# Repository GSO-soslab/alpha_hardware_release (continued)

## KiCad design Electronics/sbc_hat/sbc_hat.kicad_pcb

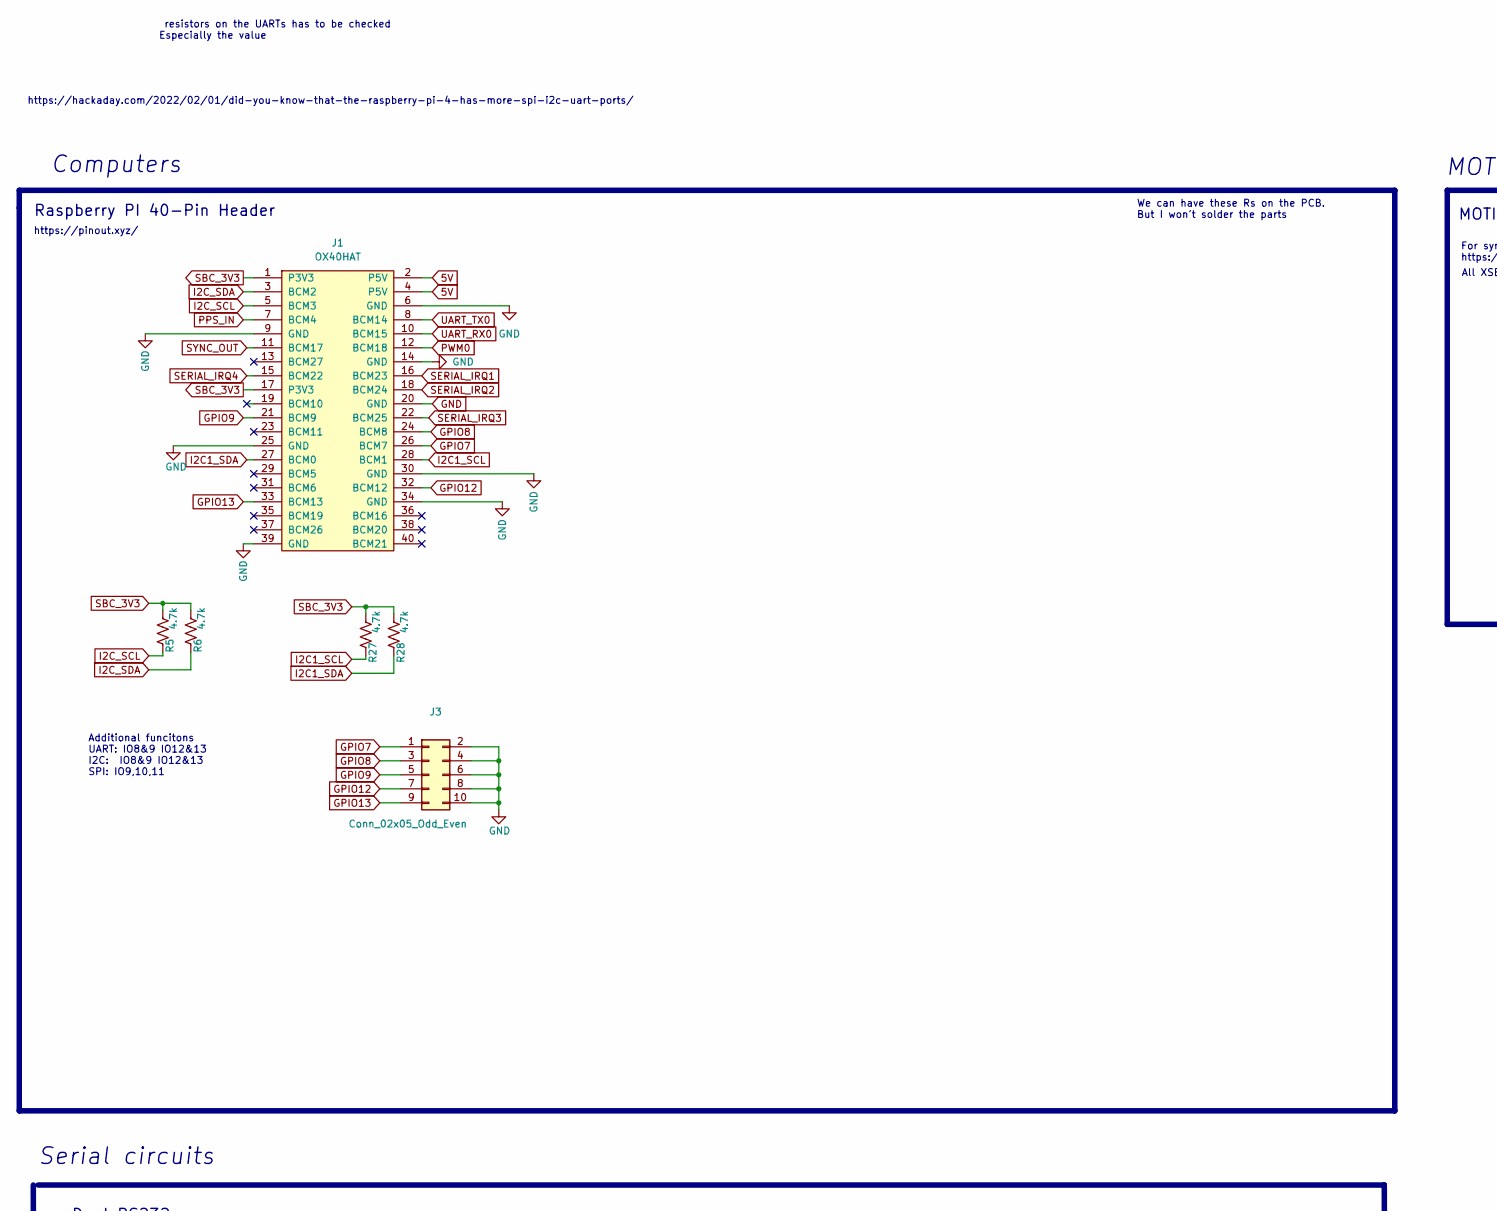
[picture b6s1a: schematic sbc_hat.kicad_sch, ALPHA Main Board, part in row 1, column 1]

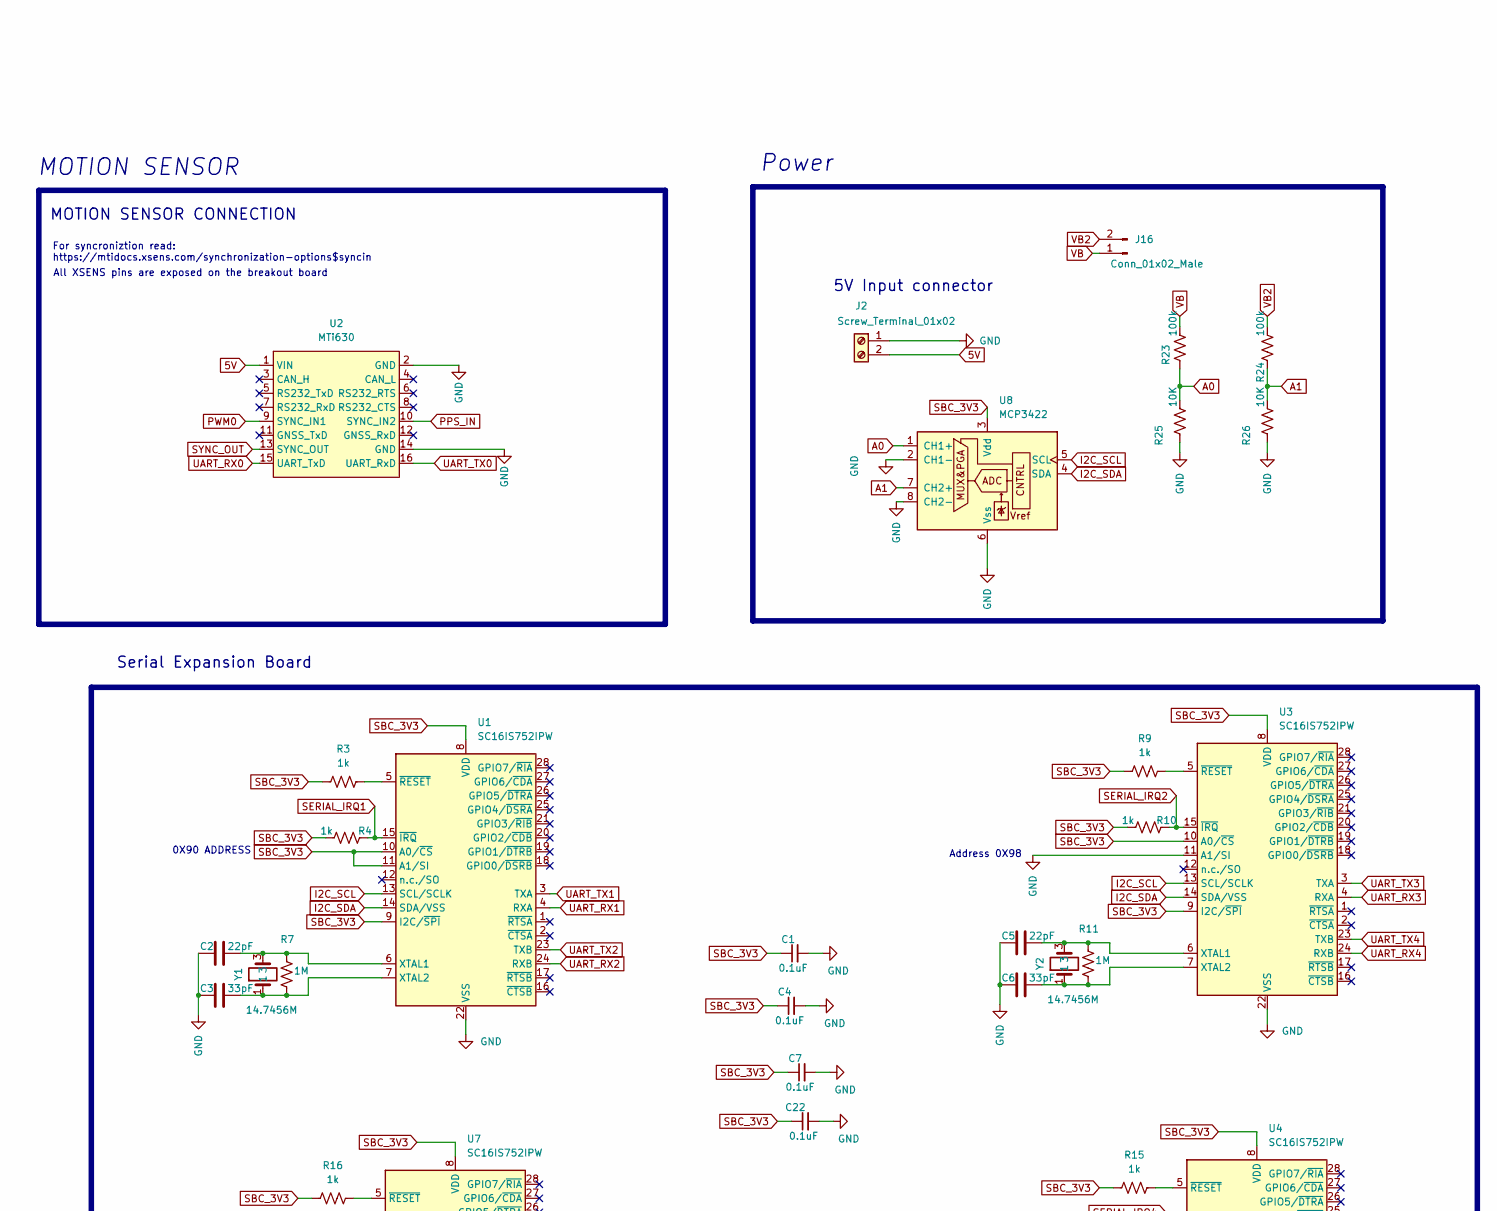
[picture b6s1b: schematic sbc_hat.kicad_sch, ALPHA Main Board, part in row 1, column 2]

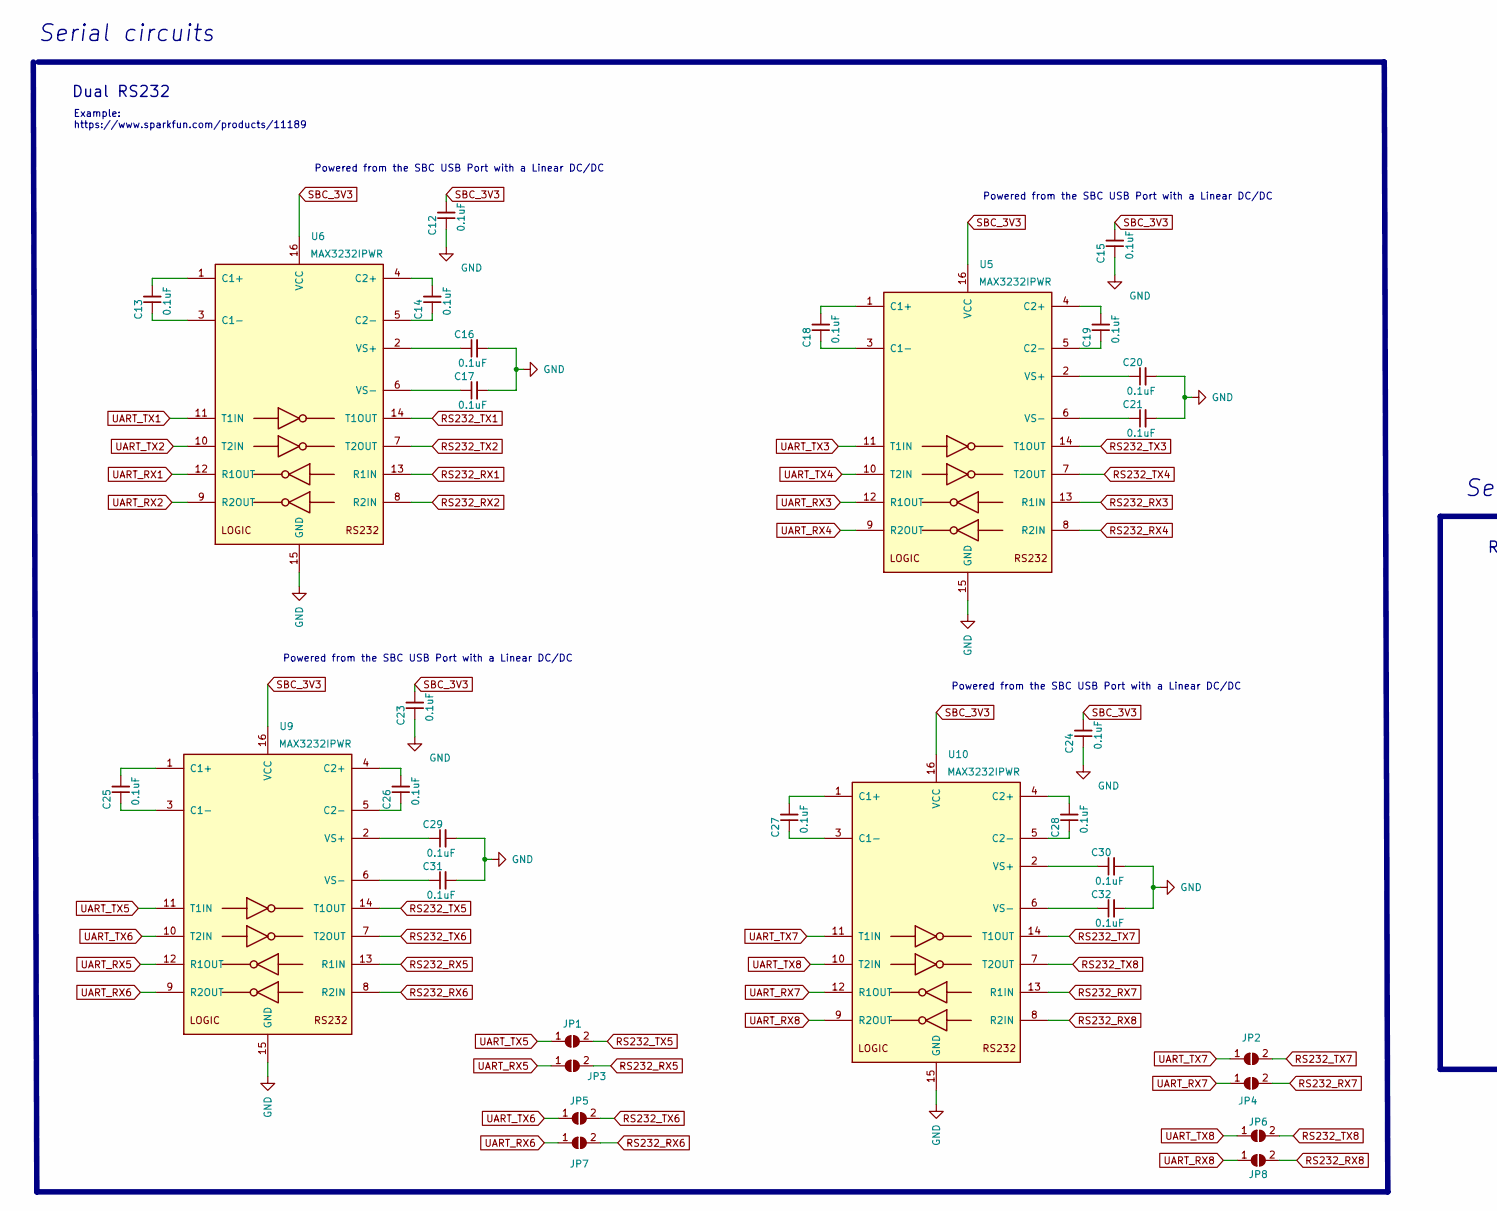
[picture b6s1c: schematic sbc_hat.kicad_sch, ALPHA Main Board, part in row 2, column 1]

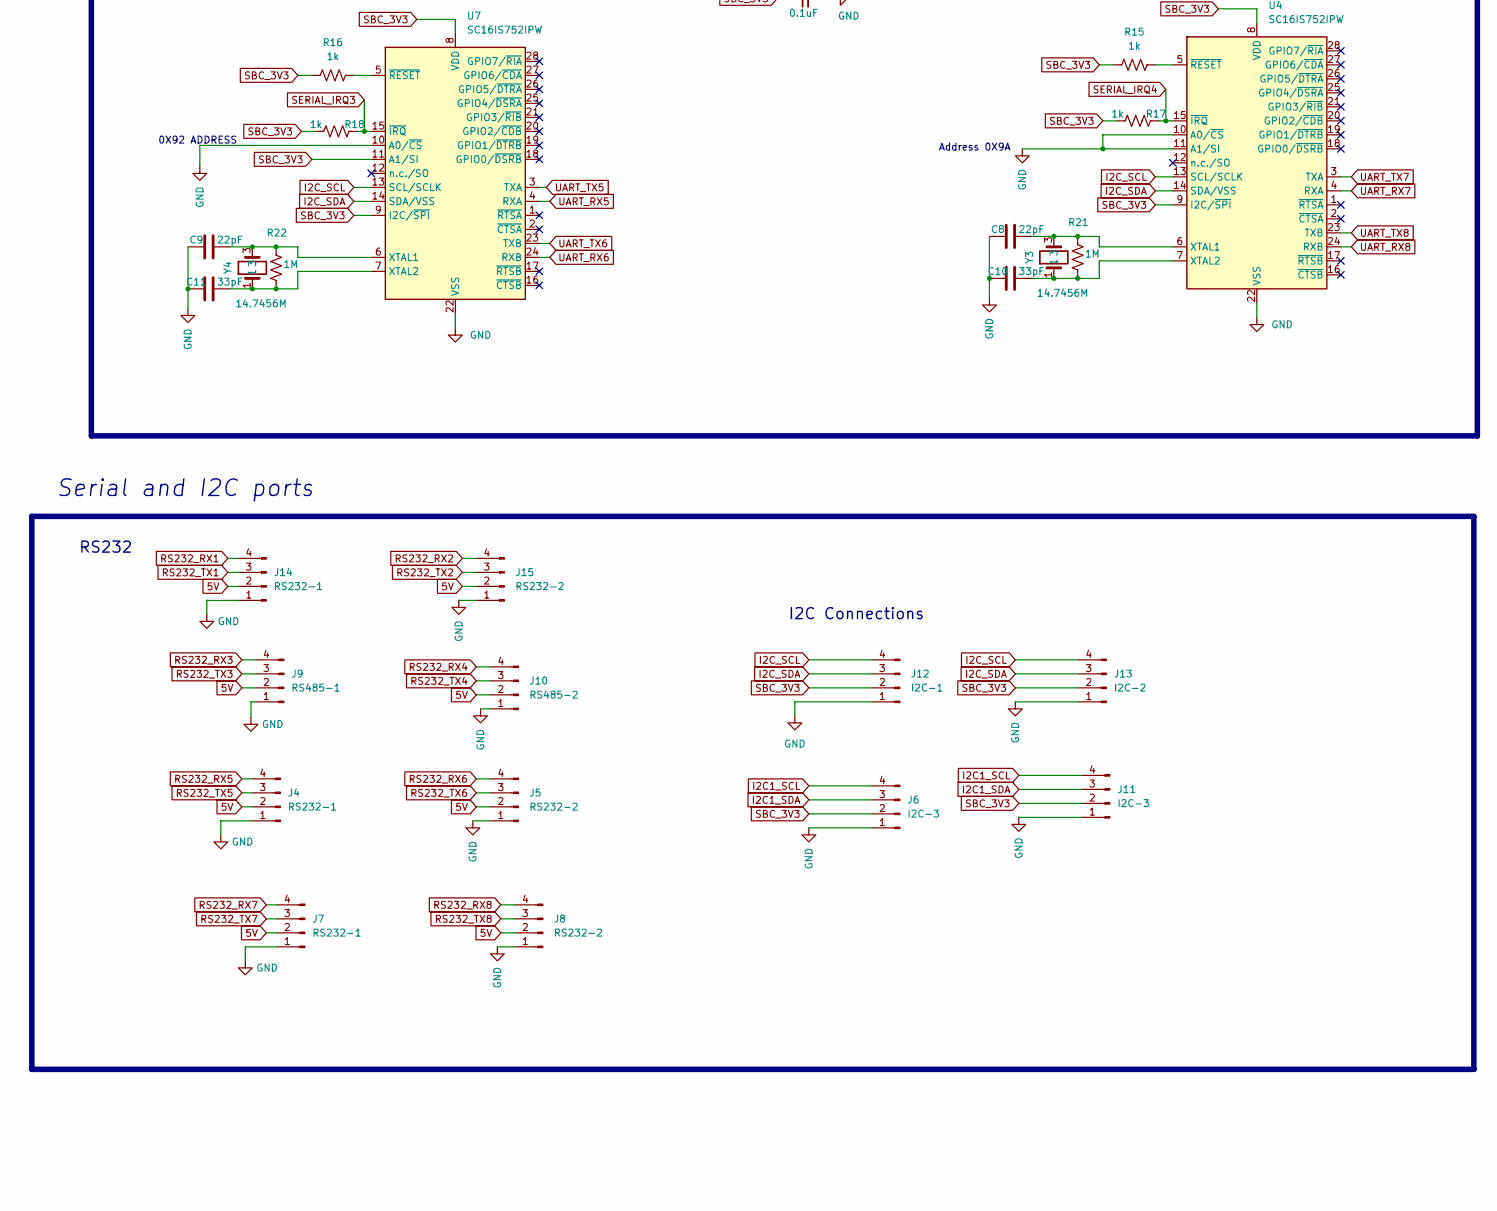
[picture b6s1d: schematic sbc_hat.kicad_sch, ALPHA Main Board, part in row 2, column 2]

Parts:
C1, C4, C7, C12, C13, C14, C15, C16, C17, C18, C19, C20, C21, C22, C23, C24, C25, C26, C27, C28, C29, C30, C31, C32: 0.1uF; C_0805_2012Metric; Manufacturer_Part_Number 0805ZC104JAT2A; Digikey Part Number 478-11627-1-ND
C2, C5, C8, C9: 22pF; C_0805_2012Metric; Manufacturer_Part_Number 08055J220FBTTR; Digikey Part Number 478-11911-1-ND
C3, C6, C10, C11: 33pF; C_0805_2012Metric; Manufacturer_Part_Number 600F330FT250XT; Digikey Part Number 1284-1049-1-ND
J1: OX40HAT; PinSocket_2x20_P2.54mm_Vertical; Mouser Part Number 474-PRT-14017
J2: Screw_Terminal_01x02; TerminalBlock_Phoenix_MPT-0,5-2-2.54_1x02_P2.54mm_Horizontal; Manufacturer_Part_Number 1725656; Mouser Part Number 651-1725656
J3: Conn_02x05_Odd_Even; PinHeader_2x05_P2.54mm_Vertical
J4, J7, J14: RS232-1; JST_SH_BM04B-SRSS-TB_1x04-1MP_P1.00mm_Vertical; Manufacturer_Part_Number 4328; Digikey Part Number 1528-4328-ND
J5, J8, J15: RS232-2; JST_SH_BM04B-SRSS-TB_1x04-1MP_P1.00mm_Vertical; Manufacturer_Part_Number 4328; Digikey Part Number 1528-4328-ND
J6, J11: I2C-3; JST_SH_BM04B-SRSS-TB_1x04-1MP_P1.00mm_Vertical; Manufacturer_Part_Number 4328; Digikey Part Number 1528-4328-ND
J9: RS485-1; JST_SH_BM04B-SRSS-TB_1x04-1MP_P1.00mm_Vertical; Manufacturer_Part_Number 4328; Digikey Part Number 1528-4328-ND
J10: RS485-2; JST_SH_BM04B-SRSS-TB_1x04-1MP_P1.00mm_Vertical; Manufacturer_Part_Number 4328; Digikey Part Number 1528-4328-ND
J12: I2C-1; JST_SH_BM04B-SRSS-TB_1x04-1MP_P1.00mm_Vertical; Manufacturer_Part_Number 4328; Digikey Part Number 1528-4328-ND
J13: I2C-2; JST_SH_BM04B-SRSS-TB_1x04-1MP_P1.00mm_Vertical; Manufacturer_Part_Number 4328; Digikey Part Number 1528-4328-ND
J16: Conn_01x02_Male; PinHeader_1x02_P2.54mm_Vertical
JP1, JP2, JP3, JP4, JP5, JP6, JP7, JP8: SolderJumper_2_Open; SolderJumper-2_P1.3mm_Open_RoundedPad1.0x1.5mm
R3, R4, R9, R10, R15, R16, R17, R18: 1k; R_0805_2012Metric; Manufacturer_Part_Number 1-2176092-8; Digikey Part Number A110543CT-ND
R5, R6, R27, R28: 4.7k; R_0805_2012Metric; Manufacturer_Part_Number ERJ-T06J472V; Mouser Part Number 667-ERJ-T06J472V
R7, R11, R21, R22: 1M; R_0805_2012Metric; Manufacturer_Part_Number ERA-6AED105V; Mouser Part Number 667-ERA-6AED105V
R23, R24: 100k; R_0805_2012Metric; Manufacturer_Part_Number ERA-6AEB104V; Mouser Part Number 667-ERA-6AEB104V
R25, R26: 10K; R_0805_2012Metric; Manufacturer_Part_Number ERA-6AEB104V; Mouser Part Number 667-ERA-6AEB104V
U1, U3, U4, U7: SC16IS752IPW; TSSOP-28_4.4x9.7mm_P0.65mm
U2: MTi630
U5, U6, U9, U10: MAX3232IPWR; TSSOP-16_4.4x5mm_P0.65mm; Manufacturer_Part_Number MAX3232IPWR; Mouser Part Number 595-MAX3232IPWR
U8: MCP3422; SOIC-8-1EP_3.9x4.9mm_P1.27mm_EP2.29x3mm
Y1, Y2, Y3, Y4: 14.7456M; Crystal_SMD_3225-4Pin_3.2x2.5mm

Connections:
5V: J1.2 (P5V), J1.4 (P5V), J2.2, J4.2, J5.2, J7.2, J8.2, J9.2, J10.2, J14.2, J15.2, U2.1 (VIN)
A0: R23.2, R25.1, U8.1 (CH1+)
A1: R24.2, R26.1, U8.7 (CH2+)
GND: C1.2, C2.1, C3.1, C4.2, C5.1, C6.1, C7.2, C8.1, C9.1, C10.1, C11.1, C12.1, C15.1, C16.2, C17.2, C20.2, C21.2, C22.2, C23.1, C24.1, C29.2, C30.2, C31.2, C32.2, J1.6 (GND), J1.9 (GND), J1.14 (GND), J1.20 (GND), J1.25 (GND), J1.30 (GND), J1.34 (GND), J1.39 (GND), J2.1, J3.2, J3.4, J3.6, J3.8, J3.10, J4.1, J5.1, J6.1, J7.1, J8.1, J9.1, J10.1, J11.1, J12.1, J13.1, J14.1, J15.1, R25.2, R26.2, U1.22 (VSS), U2.2 (GND), U2.14 (GND), U3.11 (A1/SI), U3.22 (VSS), U4.10 (A0/~CS), U4.11 (A1/SI), U4.22 (VSS), U5.15 (GND), U6.15 (GND), U7.10 (A0/~CS), U7.22 (VSS), U8.2 (CH1-), U8.6 (Vss), U8.8 (CH2-), U9.15 (GND), U10.15 (GND)
GPIO7: J1.26 (BCM7), J3.1
GPIO8: J1.24 (BCM8), J3.3
GPIO9: J1.21 (BCM9), J3.5
GPIO12: J1.32 (BCM12), J3.7
GPIO13: J1.33 (BCM13), J3.9
I2C1_SCL: J1.28 (BCM1), J6.4, J11.4, R27.1
I2C1_SDA: J1.27 (BCM0), J6.3, J11.3, R28.1
I2C_SCL: J1.5 (BCM3), J12.4, J13.4, R5.1, U1.13 (SCL/SCLK), U3.13 (SCL/SCLK), U4.13 (SCL/SCLK), U7.13 (SCL/SCLK), U8.5 (SCL)
I2C_SDA: J1.3 (BCM2), J12.3, J13.3, R6.1, U1.14 (SDA/VSS), U3.14 (SDA/VSS), U4.14 (SDA/VSS), U7.14 (SDA/VSS), U8.4 (SDA)
unnamed: C2.2, R7.1, U1.6 (XTAL1), Y1.3
unnamed: C3.2, R7.2, U1.7 (XTAL2), Y1.1
unnamed: C5.2, R11.1, U3.6 (XTAL1), Y2.3
unnamed: C6.2, R11.2, U3.7 (XTAL2), Y2.1
unnamed: C8.2, R21.1, U4.6 (XTAL1), Y3.3
unnamed: C9.2, R22.1, U7.6 (XTAL1), Y4.3
unnamed: C10.2, R21.2, U4.7 (XTAL2), Y3.1
unnamed: C11.2, R22.2, U7.7 (XTAL2), Y4.1
unnamed: C13.1, U6.3 (C1-)
unnamed: C13.2, U6.1 (C1+)
unnamed: C14.1, U6.5 (C2-)
unnamed: C14.2, U6.4 (C2+)
unnamed: C16.1, U6.2 (VS+)
unnamed: C17.1, U6.6 (VS-)
unnamed: C18.1, U5.3 (C1-)
unnamed: C18.2, U5.1 (C1+)
unnamed: C19.1, U5.5 (C2-)
unnamed: C19.2, U5.4 (C2+)
unnamed: C20.1, U5.2 (VS+)
unnamed: C21.1, U5.6 (VS-)
unnamed: C25.1, U9.3 (C1-)
unnamed: C25.2, U9.1 (C1+)
unnamed: C26.1, U9.5 (C2-)
unnamed: C26.2, U9.4 (C2+)
unnamed: C27.1, U10.3 (C1-)
unnamed: C27.2, U10.1 (C1+)
unnamed: C28.1, U10.5 (C2-)
unnamed: C28.2, U10.4 (C2+)
unnamed: C29.1, U9.2 (VS+)
unnamed: C30.1, U10.2 (VS+)
unnamed: C31.1, U9.6 (VS-)
unnamed: C32.1, U10.6 (VS-)
unnamed: R3.2, U1.5 (~RESET)
unnamed: R9.2, U3.5 (~RESET)
unnamed: R15.2, U4.5 (~RESET)
unnamed: R16.2, U7.5 (~RESET)
PPS_IN: J1.7 (BCM4), U2.10 (SYNC_IN2)
PWM0: J1.12 (BCM18), U2.9 (SYNC_IN1)
RS232_RX1: J14.4, U6.13 (R1IN)
RS232_RX2: J15.4, U6.8 (R2IN)
RS232_RX3: J9.4, U5.13 (R1IN)
RS232_RX4: J10.4, U5.8 (R2IN)
RS232_RX5: J4.4, JP3.2 (B), U9.13 (R1IN)
RS232_RX6: J5.4, JP7.2 (B), U9.8 (R2IN)
RS232_RX7: J7.4, JP4.2 (B), U10.13 (R1IN)
RS232_RX8: J8.4, JP8.2 (B), U10.8 (R2IN)
RS232_TX1: J14.3, U6.14 (T1OUT)
RS232_TX2: J15.3, U6.7 (T2OUT)
RS232_TX3: J9.3, U5.14 (T1OUT)
RS232_TX4: J10.3, U5.7 (T2OUT)
RS232_TX5: J4.3, JP1.2 (B), U9.14 (T1OUT)
RS232_TX6: J5.3, JP5.2 (B), U9.7 (T2OUT)
RS232_TX7: J7.3, JP2.2 (B), U10.14 (T1OUT)
RS232_TX8: J8.3, JP6.2 (B), U10.7 (T2OUT)
SBC_3V3: C1.1, C4.1, C7.1, C12.2, C15.2, C22.1, C23.2, C24.2, J1.1 (P3V3), J1.17 (P3V3), J6.2, J11.2, J12.2, J13.2, R3.1, R4.2, R5.2, R6.2, R9.1, R10.2, R15.1, R16.1, R17.2, R18.2, R27.2, R28.2, U1.8 (VDD), U1.9 (I2C/~SPI), U1.10 (A0/~CS), U1.11 (A1/SI), U3.8 (VDD), U3.9 (I2C/~SPI), U3.10 (A0/~CS), U4.8 (VDD), U4.9 (I2C/~SPI), U5.16 (VCC), U6.16 (VCC), U7.8 (VDD), U7.9 (I2C/~SPI), U7.11 (A1/SI), U8.3 (Vdd), U9.16 (VCC), U10.16 (VCC)
SERIAL_IRQ1: J1.16 (BCM23), R4.1, U1.15 (~IRQ)
SERIAL_IRQ2: J1.18 (BCM24), R10.1, U3.15 (~IRQ)
SERIAL_IRQ3: J1.22 (BCM25), R18.1, U7.15 (~IRQ)
SERIAL_IRQ4: J1.15 (BCM22), R17.1, U4.15 (~IRQ)
SYNC_OUT: J1.11 (BCM17), U2.13 (SYNC_OUT)
UART_RX0: J1.10 (BCM15), U2.15 (UART_TxD)
UART_RX1: U1.4 (RXA), U6.12 (R1OUT)
UART_RX2: U1.24 (RXB), U6.9 (R2OUT)
UART_RX3: U3.4 (RXA), U5.12 (R1OUT)
UART_RX4: U3.24 (RXB), U5.9 (R2OUT)
UART_RX5: JP3.1 (A), U7.4 (RXA), U9.12 (R1OUT)
UART_RX6: JP7.1 (A), U7.24 (RXB), U9.9 (R2OUT)
UART_RX7: JP4.1 (A), U4.4 (RXA), U10.12 (R1OUT)
UART_RX8: JP8.1 (A), U4.24 (RXB), U10.9 (R2OUT)
UART_TX0: J1.8 (BCM14), U2.16 (UART_RxD)
UART_TX1: U1.3 (TXA), U6.11 (T1IN)
UART_TX2: U1.23 (TXB), U6.10 (T2IN)
UART_TX3: U3.3 (TXA), U5.11 (T1IN)
UART_TX4: U3.23 (TXB), U5.10 (T2IN)
UART_TX5: JP1.1 (A), U7.3 (TXA), U9.11 (T1IN)
UART_TX6: JP5.1 (A), U7.23 (TXB), U9.10 (T2IN)
UART_TX7: JP2.1 (A), U4.3 (TXA), U10.11 (T1IN)
UART_TX8: JP6.1 (A), U4.23 (TXB), U10.10 (T2IN)
VB: J16.1, R23.1
VB2: J16.2, R24.1

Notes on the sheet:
I2C Connections
Powered from the SBC USB Port with a Linear DC/DC
0X90 ADDRESS
5V Input connector
RS232
Serial circuits
MOTION SENSOR CONNECTION
Dual RS232
Power
Address 0X9A
Example: https://www.sparkfun.com/products/11189
Additional funcitons UART: IO8&9 IO12&13 I2C: IO8&9 IO12&13 SPI: IO9,10,11
All XSENS pins are exposed on the breakout board
Computers
0X92 ADDRESS
For syncroniztion read: https://mtidocs.xsens.com/synchronization-options$syncin
We can have these Rs on the PCB. But I won't solder the parts
https://pinout.xyz/
Raspberry PI 40-Pin Header
https://hackaday.com/2022/02/01/did-you-know-that-the-raspberry-pi-4-has-more-spi-i2c-uart-ports/
MOTION SENSOR
resistors on the UARTs has to be checked Especially the value
Address 0X98
Serial Expansion Board
Serial and I2C ports

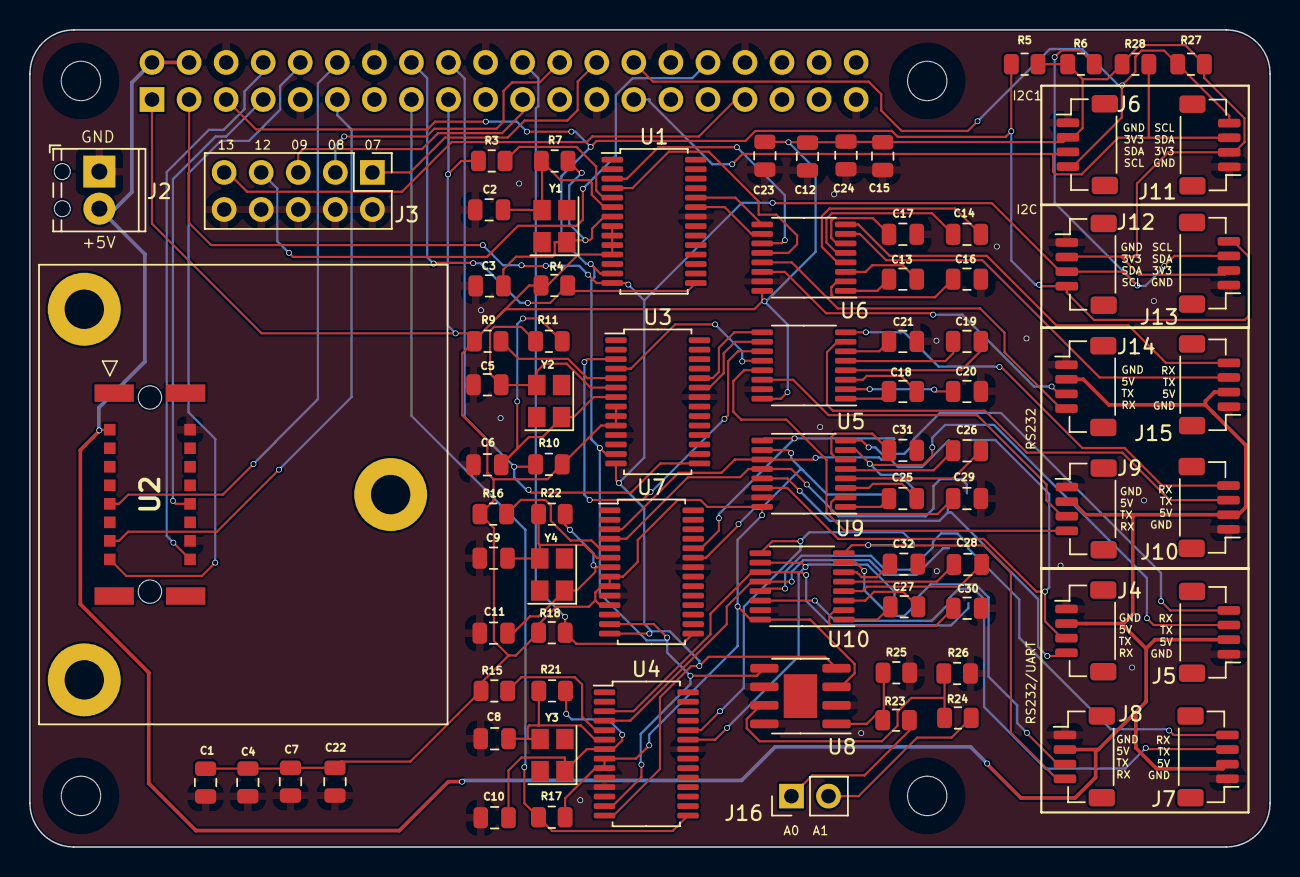
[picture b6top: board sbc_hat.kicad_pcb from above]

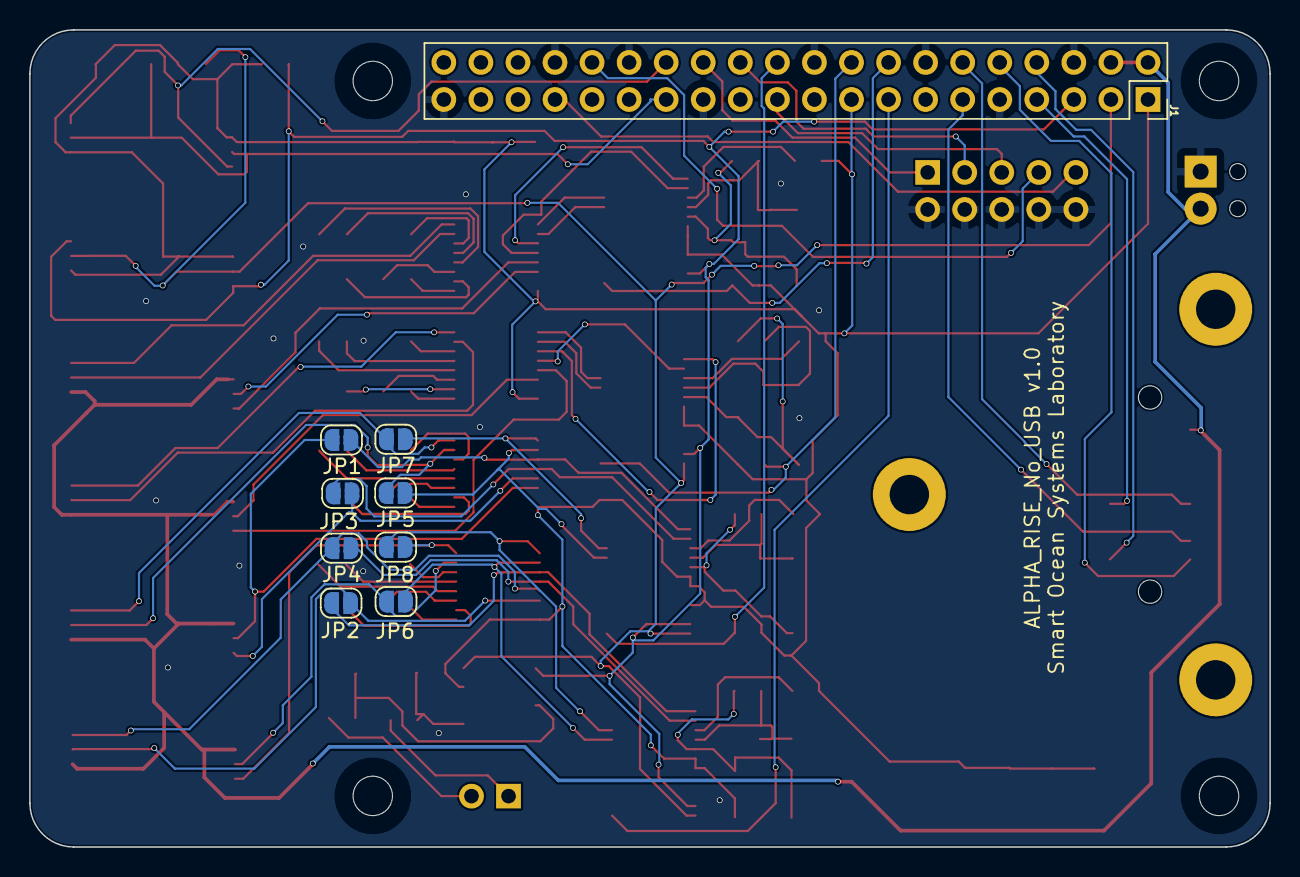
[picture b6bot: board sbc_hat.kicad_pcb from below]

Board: 2 copper layers, 85.0 x 56.0 mm, 94 parts (9 on the bottom side), 93 nets.

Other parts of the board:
MH1, MH2, MH3, MH4: MountingHole_2.7mm_M2.5

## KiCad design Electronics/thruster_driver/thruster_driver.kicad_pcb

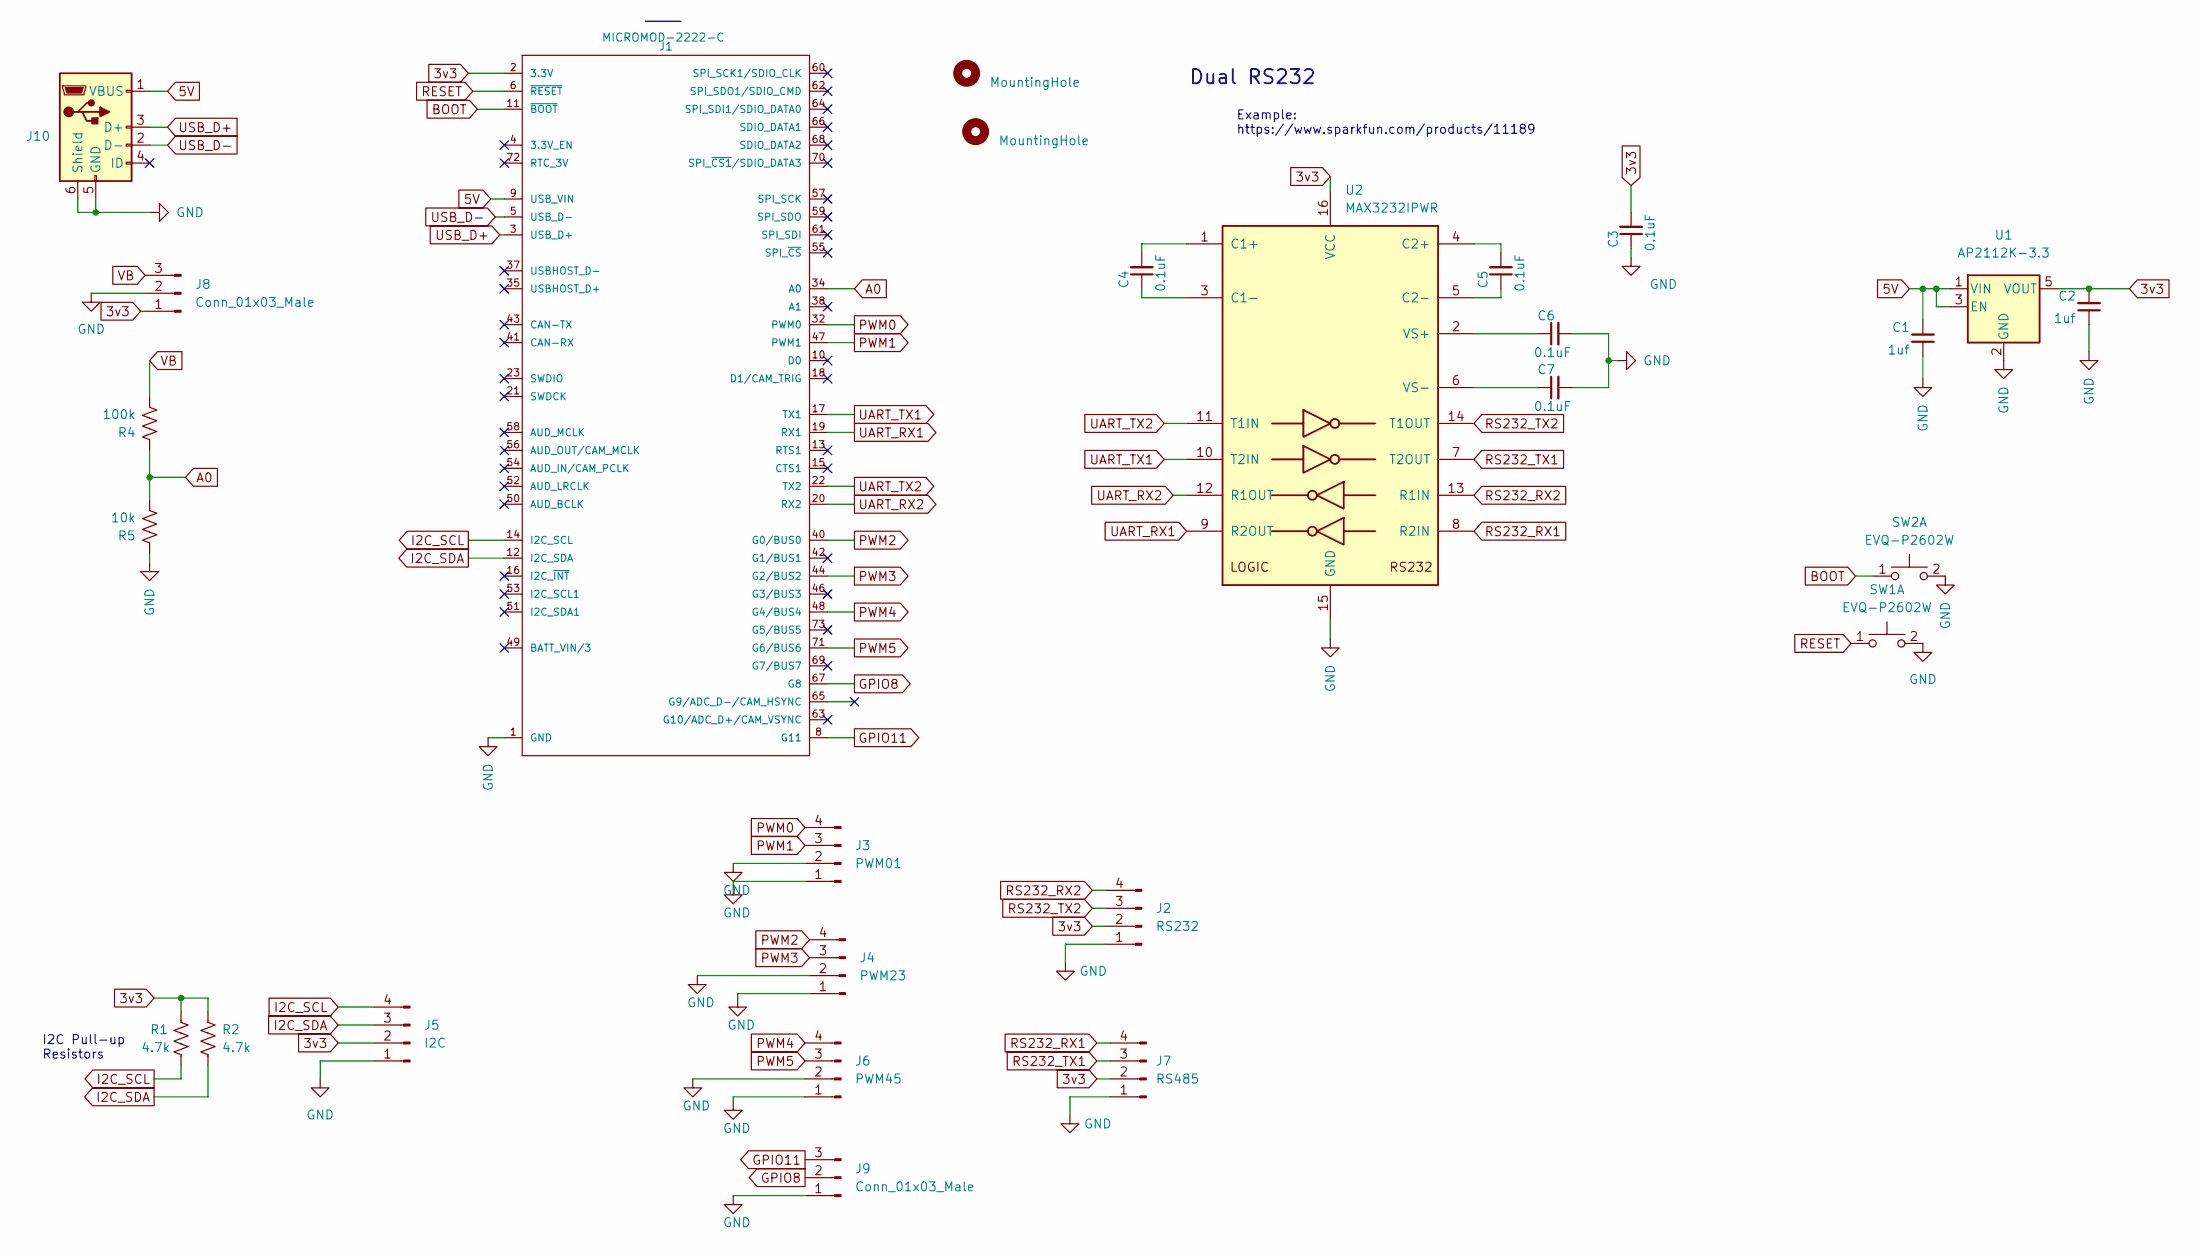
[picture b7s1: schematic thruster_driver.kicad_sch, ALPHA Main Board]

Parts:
C1, C2: 1uf; C_0805_2012Metric; Manufacturer_Part_Number 0805YC106KAT2A; Mouser Part Number 581-0805YC106KAT2A
C3, C4, C5, C6, C7: 0.1uF; C_0805_2012Metric; Manufacturer_Part_Number 0805ZC104JAT2A; Digikey Part Number 478-11627-1-ND
H1, H2: MountingHole; MountingHole_2.2mm_M2_ISO7380_Pad
J1: MICROMOD-2222-C; M.2-CONNECTOR-E; Manufacturer_Part_Number KIT-16549; Digikey Part Number 1568-KIT-16549-ND
J2: RS232; JST_SH_BM04B-SRSS-TB_1x04-1MP_P1.00mm_Vertical; Manufacturer_Part_Number 4328; Digikey Part Number 1528-4328-ND
J3: PWM01; JST_SH_BM04B-SRSS-TB_1x04-1MP_P1.00mm_Vertical; Manufacturer_Part_Number 4328; Digikey Part Number 1528-4328-ND
J4: PWM23; JST_SH_BM04B-SRSS-TB_1x04-1MP_P1.00mm_Vertical; Manufacturer_Part_Number 4328; Digikey Part Number 1528-4328-ND
J5: I2C; JST_SH_BM04B-SRSS-TB_1x04-1MP_P1.00mm_Vertical; Manufacturer_Part_Number 4328; Digikey Part Number 1528-4328-ND
J6: PWM45; JST_SH_BM04B-SRSS-TB_1x04-1MP_P1.00mm_Vertical; Manufacturer_Part_Number 4328; Digikey Part Number 1528-4328-ND
J7: RS485; JST_SH_BM04B-SRSS-TB_1x04-1MP_P1.00mm_Vertical; Manufacturer_Part_Number 4328; Digikey Part Number 1528-4328-ND
J8, J9: Conn_01x03_Male; PinHeader_1x03_P2.54mm_Vertical
J10: USB_B_Micro; USB_Micro-B_Amphenol_10118194_Horizontal; Manufacturer_Part_Number 10118194-0001LF; Digikey Part Number 609-4618-2-ND
R1, R2: 4.7k; R_0805_2012Metric; Manufacturer_Part_Number ERJ-T06J472V; Mouser Part Number 667-ERJ-T06J472V
R4: 100k; R_0805_2012Metric; Manufacturer_Part_Number ERJ-T06J472V; Mouser Part Number 667-ERJ-T06J472V
R5: 10k; R_0805_2012Metric; Manufacturer_Part_Number ERJ-T06J472V; Mouser Part Number 667-ERJ-T06J472V
SW1, SW2: EVQ-P2602W; SW_SPST_EVQP2
U1: AP2112K-3.3; SOT-23-5
U2: MAX3232IPWR; TSSOP-16_4.4x5mm_P0.65mm; Manufacturer_Part_Number MAX3232IPWR; Mouser Part Number 595-MAX3232IPWR

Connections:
3v3: C2.2, C3.2, J1.2 (3.3V), J1.74 (3.3V), J2.2, J5.2, J7.2, J8.1, R1.1, R2.1, U1.5 (VOUT), U2.16 (VCC)
5V: C1.2, J1.9 (USB_VIN), J10.1 (VBUS), U1.1 (VIN), U1.3 (EN)
A0: J1.34 (A0), R4.1, R5.2
BOOT: J1.11 (~BOOT), SW2.1 (C); also elsewhere on the board
GND: C1.1, C2.1, C3.1, C6.2, C7.2, J1.1 (GND), J1.7 (GND), J1.33 (GND), J1.36 (GND), J1.39 (GND), J1.45 (GND), J1.75 (GND), J2.1, J3.1, J3.2, J4.1, J4.2, J5.1, J6.1, J6.2, J7.1, J8.2, J9.1, J10.5 (GND), J10.6 (Shield), R5.1, SW1.2 (D), SW2.2 (D), U1.2 (GND), U2.15 (GND); also elsewhere on the board
GPIO8: J1.67 (G8), J9.2
GPIO11: J1.8 (G11), J9.3
I2C_SCL: J1.14 (I2C_SCL), J5.4, R1.2
I2C_SDA: J1.12 (I2C_SDA), J5.3, R2.2
unnamed: C4.1, U2.3 (C1-)
unnamed: C4.2, U2.1 (C1+)
unnamed: C5.1, U2.5 (C2-)
unnamed: C5.2, U2.4 (C2+)
unnamed: C6.1, U2.2 (VS+)
unnamed: C7.1, U2.6 (VS-)
PWM0: J1.32 (PWM0), J3.4
PWM1: J1.47 (PWM1), J3.3
PWM2: J1.40 (G0/BUS0), J4.4
PWM3: J1.44 (G2/BUS2), J4.3
PWM4: J1.48 (G4/BUS4), J6.4
PWM5: J1.71 (G6/BUS6), J6.3
RESET: J1.6 (~RESET), SW1.1 (C); also elsewhere on the board
RS232_RX1: J7.4, U2.8 (R2IN)
RS232_RX2: J2.4, U2.13 (R1IN)
RS232_TX1: J7.3, U2.7 (T2OUT)
RS232_TX2: J2.3, U2.14 (T1OUT)
UART_RX1: J1.19 (RX1), U2.9 (R2OUT)
UART_RX2: J1.20 (RX2), U2.12 (R1OUT)
UART_TX1: J1.17 (TX1), U2.10 (T2IN)
UART_TX2: J1.22 (TX2), U2.11 (T1IN)
USB_D+: J1.3 (USB_D+), J10.3 (D+)
USB_D-: J1.5 (USB_D-), J10.2 (D-)
VB: J8.3, R4.2

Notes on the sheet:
I2C Pull-up Resistors
Dual RS232
Example: https://www.sparkfun.com/products/11189

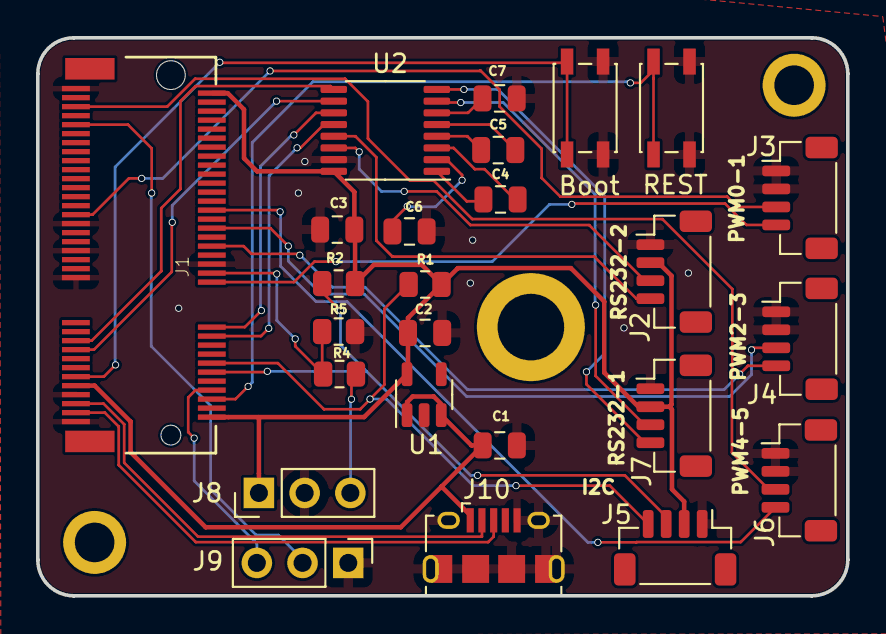
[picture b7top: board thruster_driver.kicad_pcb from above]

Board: 2 copper layers, 45.0 x 31.0 mm, 27 parts (0 on the bottom side), 33 nets.

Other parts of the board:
Boot: EVQ-P2602W; SW_SPST_EVQP2
REST: EVQ-P2602W; SW_SPST_EVQP2

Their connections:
BOOT: Boot.1 (C); also elsewhere on the board
GND: Boot.2 (D), REST.2 (D); also elsewhere on the board
RESET: REST.1 (C); also elsewhere on the board

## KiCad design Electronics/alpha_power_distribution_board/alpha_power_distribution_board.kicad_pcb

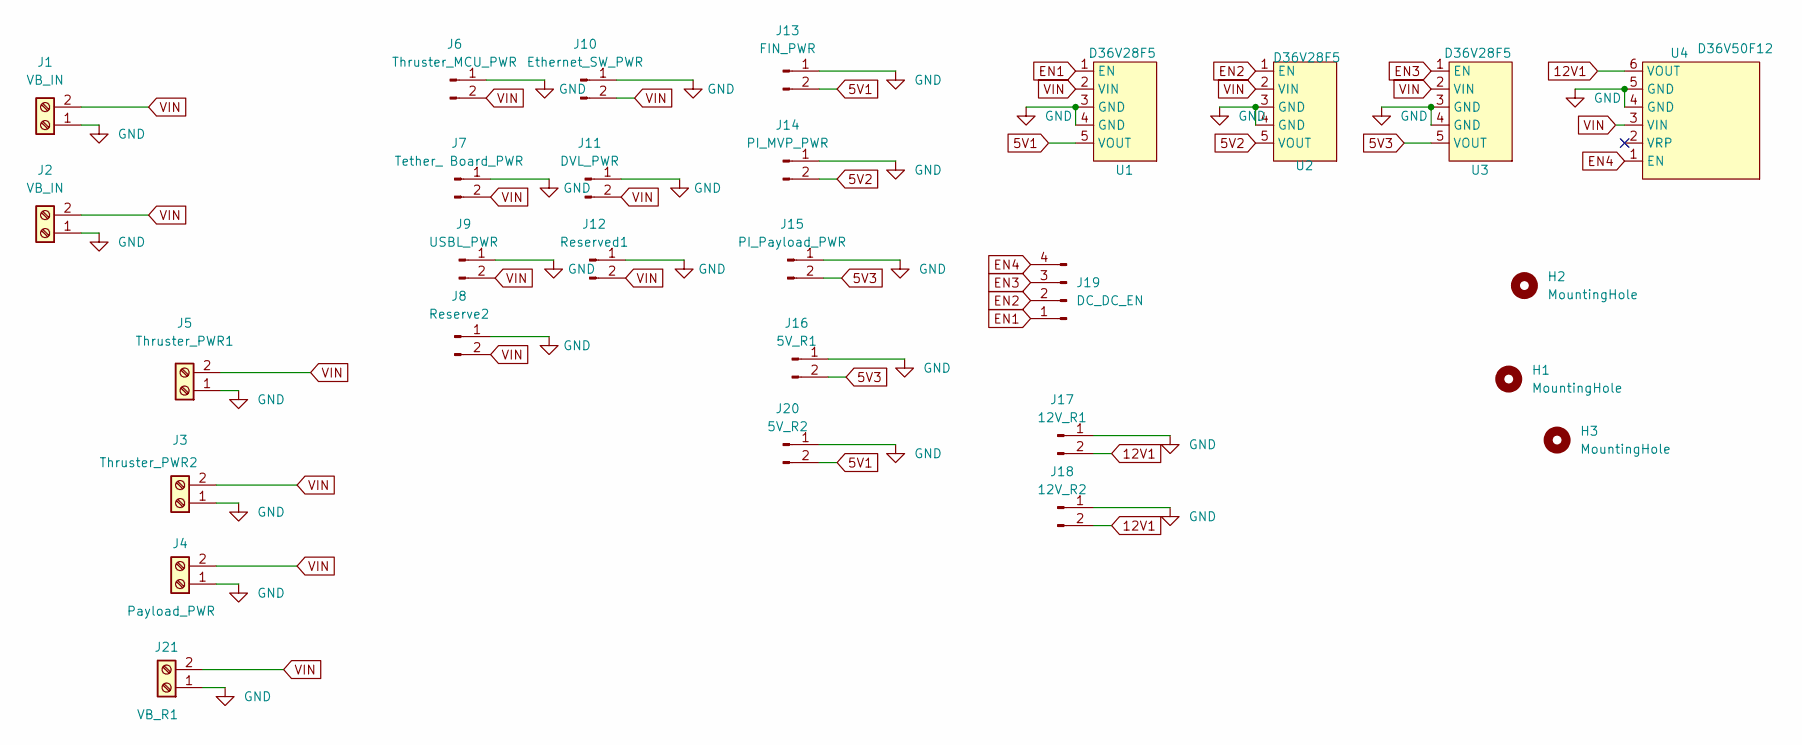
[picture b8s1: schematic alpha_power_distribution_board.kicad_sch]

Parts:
H1, H2, H3: MountingHole; MountingHole_2.7mm_M2.5
J1, J2: VB_IN; Pololu_5mm
J3: Thruster_PWR2; Pololu_5mm
J4: Payload_PWR; Pololu_5mm
J5: Thruster_PWR1; Pololu_5mm
J6: Thruster_MCU_PWR; JST_XH_B02B-XH-A_02x2.50mm_Straight
J7: Tether_ Board_PWR; JST_XH_B02B-XH-A_02x2.50mm_Straight
J8: Reserve2; JST_XH_B02B-XH-A_02x2.50mm_Straight
J9: USBL_PWR; JST_XH_B02B-XH-A_02x2.50mm_Straight
J10: Ethernet_SW_PWR; JST_XH_B02B-XH-A_02x2.50mm_Straight
J11: DVL_PWR; JST_XH_B02B-XH-A_02x2.50mm_Straight
J12: Reserved1; JST_XH_B02B-XH-A_02x2.50mm_Straight
J13: FIN_PWR; JST_XH_B02B-XH-A_02x2.50mm_Straight
J14: PI_MVP_PWR; JST_XH_B02B-XH-A_02x2.50mm_Straight
J15: PI_Payload_PWR; JST_XH_B02B-XH-A_02x2.50mm_Straight
J16: 5V_R1; JST_XH_B02B-XH-A_02x2.50mm_Straight
J17: 12V_R1; JST_XH_B02B-XH-A_02x2.50mm_Straight
J18: 12V_R2; JST_XH_B02B-XH-A_02x2.50mm_Straight
J19: DC_DC_EN; JST_SH_BM04B-SRSS-TB_1x04-1MP_P1.00mm_Vertical; Manufacturer_Part_Number 4328; Digikey Part Number 1528-4328-ND
J20: 5V_R2; JST_XH_B02B-XH-A_02x2.50mm_Straight
J21: VB_R1; Pololu_5mm
U1, U2, U3: D36V28F5
U4: D36V50F12

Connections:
5V1: J13.2, J20.2, U1.5 (VOUT)
5V2: J14.2, U2.5 (VOUT)
5V3: J15.2, J16.2, U3.5 (VOUT)
12V1: J17.2, J18.2, U4.6 (VOUT)
EN1: J19.1, U1.1 (EN)
EN2: J19.2, U2.1 (EN)
EN3: J19.3, U3.1 (EN)
EN4: J19.4, U4.1 (EN)
GND: J1.1, J2.1, J3.1, J4.1, J5.1, J6.1, J7.1, J8.1, J9.1, J10.1, J11.1, J12.1, J13.1, J14.1, J15.1, J16.1, J17.1, J18.1, J20.1, J21.1, U1.3 (GND), U1.4 (GND), U2.3 (GND), U2.4 (GND), U3.3 (GND), U3.4 (GND), U4.4 (GND), U4.5 (GND)
VIN: J1.2, J2.2, J3.2, J4.2, J5.2, J6.2, J7.2, J8.2, J9.2, J10.2, J11.2, J12.2, J21.2, U1.2 (VIN), U2.2 (VIN), U3.2 (VIN), U4.3 (VIN)
